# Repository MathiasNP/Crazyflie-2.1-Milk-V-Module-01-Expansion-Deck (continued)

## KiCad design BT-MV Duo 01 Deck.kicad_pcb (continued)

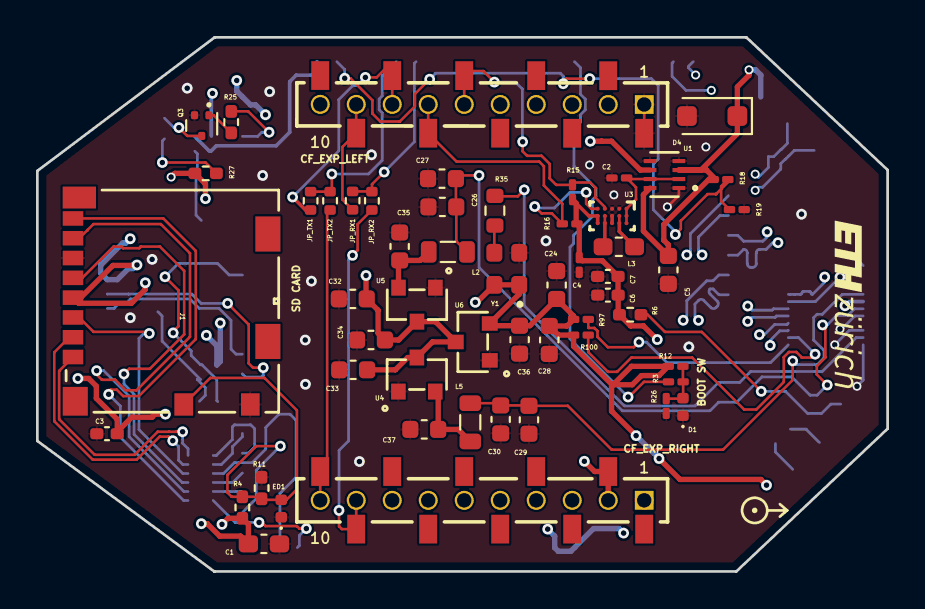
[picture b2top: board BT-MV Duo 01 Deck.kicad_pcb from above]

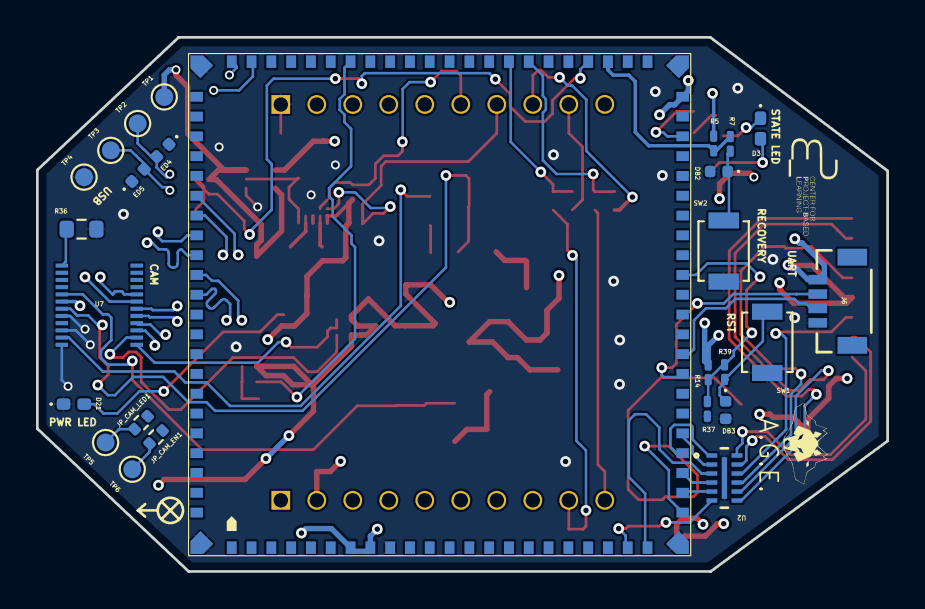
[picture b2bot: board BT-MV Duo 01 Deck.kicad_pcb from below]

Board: 4 copper layers, 47.2 x 29.7 mm, 81 parts (26 on the bottom side), 62 nets.

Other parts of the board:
EXP_ORIENTATION: VAL**; EXP_ORIENTATION

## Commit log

2026-01-14 Create Test
2026-01-21 Final update
